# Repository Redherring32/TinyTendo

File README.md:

# Tiny 'Tendo
An open-source Gameboy sized handheld NES using real hardware

## DISCLAIMER:

TinyTendo is a complex project that has taken a ton of effort, and despite now being open source should still be considered somewhat experimental, should you find anything that isn't quite right, please file an issue.

Additionally, TinyTendo requires physically cutting and grinding ORIGINAL NES chips down smaller, this is a difficult, tedious, and risky process. 

You could KILL the chips if this is not done correctly, do this at your own risk, I am not responsible for damage to any hardware resulting from attempting to build this project.

## Repository Structure:

* Hardware: Contains all files relating to the hardware design for the various PCBs used for this project

* Software: Contains the software required for the brightness mod PCB

* 3D-CAD: Contains design files for the housing design

The files required to order PCBs can be found under releases.

This project is a derivitive of OpenTendo, and OpenTendo-Toploader, and is licensed accordingly. Please read the LICENSE in the repository for more info.

Since this project is open-source you may do as you like with it, whether that is to make TinyTendo for personal use, sell PCBs or assembled handhelds, or to use the provided info for further custom PCB work/designs.

*Note:* 
REAL NES chips from a real NES are required, clone chips cannot be used without some redesign of the motherboard, as they cannot be trimmed down as small.
A version of the PCB that supports them would be relatively easy to make, but I myself have no interest in doing so. (PRs to add a "clone" branch are welcome!)

And finally, I am NOT an EE, if you are at all disgusted by any aspect of the PCB designs, I am sorry. (PRs for this are also welcome :P)

## TO-DO:

* Write chip trimming guide to go over workflow and best practices

* Update readme image to reflect current hardware revision

* Figure out what I am forgetting to add to TO-DO

## License:

Licensed under
the TAPR Open Hardware License (www.tapr.org/OHL)

©Redherring32 2019-2022

All hardware contained within this repository was designed by me except the Brightness mod PCB.
The brightness mod PCB was designed by YveltalGriffin, and has been licensed under TAPR OHL with permission from the author.
The brightness PCB was designed using Eagle, all other hardware was designed using KiCAD.
The Brightness software was written by YveltalGriffin, and has been licensed under MIT with permission from the author, see LICENSE in software folder for details.
## Credits

In no particular order:

*FenrisWolfRetro* -Creating the wiring diagram in the Hardware folder.

*YveltalGriffin* -Designed the brightness mod PCB, and wrote the code for it, and was just a tremendous help.

*DiscoStarslayer* -Helping to inspire me to trim the chipset, without his joking suggestion to dremel the package and solder to the leads, I would not have started researching chip trimming.

*lidnariq* -Helping me diagnose my idiotic design blunders, might not have had the motivation to keep going on the project without their help.

*BucketMouse* -Designing cartridge PCBs for TinyTendo, and help with diagnosis work.

*MuraMasa* -Help with diagnosis work, sharing KiCAD footprints for early protos cause I kept messing mine up. :)

And to all of the awesome people in NESDev, you guys rock.

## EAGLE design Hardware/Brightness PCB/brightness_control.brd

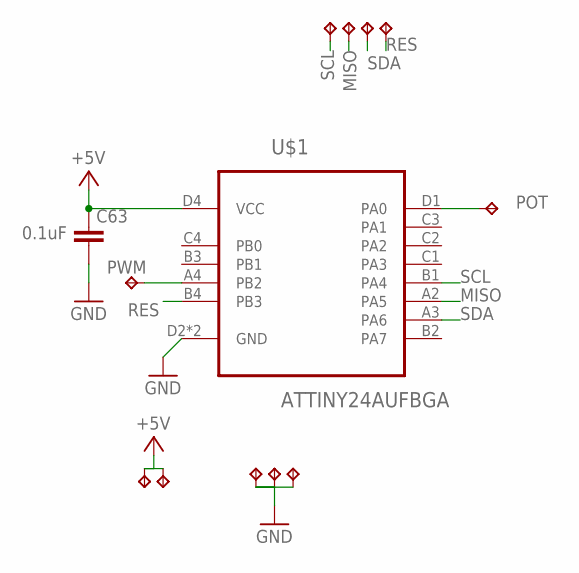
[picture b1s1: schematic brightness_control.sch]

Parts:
C63: 0.1uF; C0402
TP1, TP3, TP4, TP5, TP6, TP7, TP8, TP10, TP11, TP12, TP13: TPTP12R; TP12R
U$1: ATTINY24AUFBGA; UFBGA-15

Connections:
+5V: C63.1, TP3.TP, TP4.TP, U$1.D4 (VCC)
GND: C63.2, TP1.TP, TP5.TP, TP6.TP, U$1.D2 (GND), U$1.D3 (GND)
MISO: TP11.TP, U$1.A2 (PA5)
POT: TP7.TP, U$1.D1 (PA0)
PWM: TP8.TP, U$1.A4 (PB2)
RES: TP13.TP, U$1.B4 (PB3)
SCL: TP10.TP, U$1.B1 (PA4)
SDA: TP12.TP, U$1.A3 (PA6)

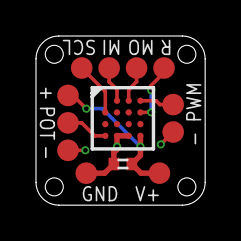
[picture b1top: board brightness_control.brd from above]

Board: 2 copper layers, 9.4 x 9.4 mm, 13 parts (0 on the bottom side), 8 nets.

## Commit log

2022-05-28 + Add Working Files + Initial Readme Draft
2022-05-29 + Updated README.md + Fixed schematic/pinout error with Q1, and added decoupling capacitor to Composite Amp
2022-06-15 + Motherboard is now V1.0 + Redesigned ScreenReg for improved reliability + Added both versions of ChargeBoost + Remove now redundant files/directories
2022-08-25 +Remove redundant files
2022-08-25 Update TO-DO
2022-09-04 Rename Motherboard.md to readme.md
2022-09-04 + Added TinyTendo Cart Shell CAD files
2022-09-06 + Updated FFC footprint on Cart Slot and Cart-Test
2022-09-06 Fixed typo, whoops!
2022-09-06 Update README.md
    Update Credits
    Update To-do
2022-09-14 Redid ChargeBoost layout, and added EN pull up, and RST capacitor
2022-10-01 + Fixed error on InCU1 layer + Added missing pads for audio amp power + Removed redundant autosave files
2022-11-20 +Update Motherboard to use more available SiT2001B oscillator.
2023-03-31 + Fixed isue where Cart slot would strain screwposts overtime + Updated Cartridge shell design to make printing easier, and make room for TNY-TKROM boards
2024-01-18 + Corrected duplicate reference error in Chargeboost.sch
    + Made changes to Audio Amp PCB to improve screwpost locations
    + Made changes to Button PCB to improve screwpost locations
    + Moved screen up 6mm to even out bezels on shell
    + Altered shell to improve screwpost placement, and add optional suppport for threaded inserts
    + Added 2 new shell variants, 1 with a logo via multicolor printing and threaded inserts, 1 with just threaded inserts
